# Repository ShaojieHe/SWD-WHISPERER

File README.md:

# SWD-WHISPERER
Custom DAPLink Hardware Design using AIR32F103Cx, This Version of hardware support SWD, JTAG, USB CDC, **ITM Trace/SWO**

Also this repo contain an [addon project](https://github.com/ShaojieHe/SWD-WHISPERER/tree/3225_crystal/standardJTAG_ADAPTER) to convert custom pinout to standard JTAG pinout for better debugging experience.

Licenced under CERN OHL v2 Permissive

## Pre-Built Custom DAPLink Firmware

[Github Repo](https://github.com/ShaojieHe/DAPLink-Extra)

[AIR32F10x Pre-Release](https://github.com/ShaojieHe/DAPLink-Extra/releases/tag/air32-pre-release)

## PCB Schematic
[Schematic](https://github.com/ShaojieHe/SWD-WHISPERER/blob/3225_crystal/DAPLink/air.pdf)

## PCB 3D Image

## How to Modify

This is an KiCad Project Design on version 6.0.9, You need an KiCad's Version > 6 to open it and play it around :)

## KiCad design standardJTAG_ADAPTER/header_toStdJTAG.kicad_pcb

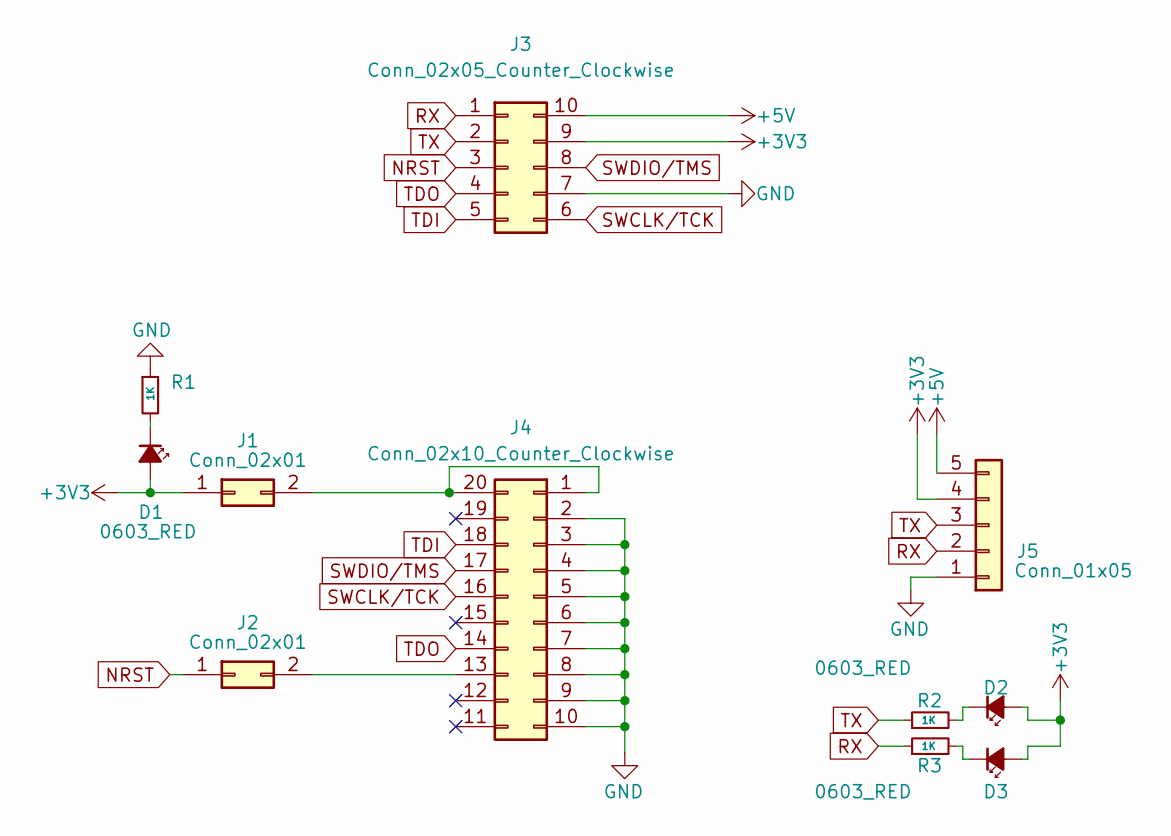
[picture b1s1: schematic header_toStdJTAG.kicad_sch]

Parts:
D1, D2, D3: 0603_RED; LED_0603_1608Metric
J1, J2: Conn_02x01; PinHeader_2x01_P2.54mm_Vertical
J3: Conn_02x05_Counter_Clockwise; 2.54_2X5
J4: Conn_02x10_Counter_Clockwise; 2.54_2X10
J5: Conn_01x05; PinHeader_1x05_P2.54mm_Vertical
R1, R2, R3: 1K; R_0603_1608Metric

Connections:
+3V3: D1.2 (A), D2.2 (A), D3.2 (A), J1.1, J3.9, J5.4
+5V: J3.10, J5.5
GND: J3.7, J4.2, J4.3, J4.4, J4.5, J4.6, J4.7, J4.8, J4.9, J4.10, J5.1, R1.1
NRST: J2.1, J3.3
unnamed: D1.1 (K), R1.2
unnamed: D2.1 (K), R2.2
unnamed: D3.1 (K), R3.2
unnamed: J1.2, J4.1, J4.20
unnamed: J2.2, J4.13
RX: J3.1, J5.2, R3.1
SWCLK/TCK: J3.6, J4.16
SWDIO/TMS: J3.8, J4.17
TDI: J3.5, J4.18
TDO: J3.4, J4.14
TX: J3.2, J5.3, R2.1

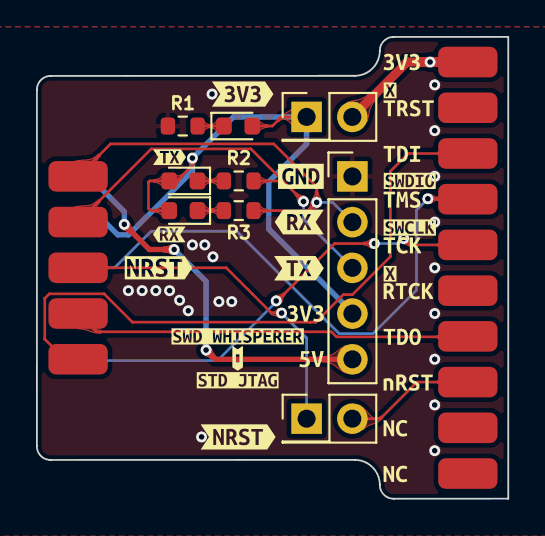
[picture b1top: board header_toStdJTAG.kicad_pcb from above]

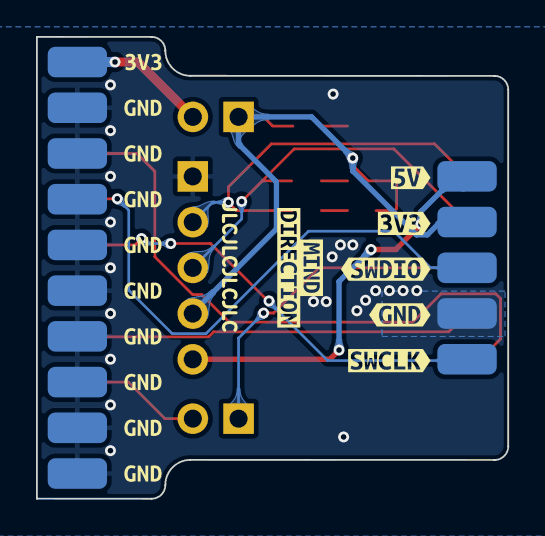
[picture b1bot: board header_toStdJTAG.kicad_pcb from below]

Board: 2 copper layers, 26.2 x 25.7 mm, 56 parts (18 on the bottom side), 15 nets.

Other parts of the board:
e: MY_LOGO
kibuzzard-632C5A4E: G***; kibuzzard-632C5A4E
kibuzzard-632C5A5B: G***; kibuzzard-632C5A5B
kibuzzard-632C5A6C: G***; kibuzzard-632C5A6C
kibuzzard-632C5A7C: G***; kibuzzard-632C5A7C
kibuzzard-632C5A8E: G***; kibuzzard-632C5A8E
kibuzzard-632C5A78: G***; kibuzzard-632C5A78
kibuzzard-632C5AAA: G***; kibuzzard-632C5AAA
kibuzzard-632C5AB4: G***; kibuzzard-632C5AB4
kibuzzard-632C5ABC: G***; kibuzzard-632C5ABC
kibuzzard-632C5B86: G***; kibuzzard-632C5B86
kibuzzard-632C5BCD: G***; kibuzzard-632C5BCD
kibuzzard-632C5CBE: G***; kibuzzard-632C5CBE
kibuzzard-632C5D1, kibuzzard-632C5D2, kibuzzard-632C5D3, kibuzzard-632C5D4, kibuzzard-632C5D5, kibuzzard-632C5D6, kibuzzard-632C5D7, kibuzzard-632C5D8, kibuzzard-632C5D89: G***; kibuzzard-632C5D89
kibuzzard-632C5D32: G***; kibuzzard-632C5D32
kibuzzard-632C5EE0: G***; kibuzzard-632C5EE0
kibuzzard-632C5EFB: G***; kibuzzard-632C5EFB
kibuzzard-632C5F3E: G***; kibuzzard-632C5F3E
kibuzzard-632C57D4: G***; kibuzzard-632C57D4
kibuzzard-632C57F8: G***; kibuzzard-632C57F8
kibuzzard-632C60B1: G***; kibuzzard-632C60B1
kibuzzard-632C60B5: G***; kibuzzard-632C60B5
kibuzzard-632C60E7: G***; kibuzzard-632C60E7
kibuzzard-632C575C: G***; kibuzzard-632C575C
kibuzzard-632C580A: G***; kibuzzard-632C580A
kibuzzard-632C584F: G***; kibuzzard-632C584F
kibuzzard-632C5768: G***; kibuzzard-632C5768
kibuzzard-632C5841: G***; kibuzzard-632C5841
kibuzzard-632C5933, kibuzzard-632C5933#2: G***; kibuzzard-632C5933
kibuzzard-632C6056: G***; kibuzzard-632C6056
kibuzzard-632C6067: G***; kibuzzard-632C6067
kibuzzard-632C6200, kibuzzard-632C6200#2: G***; kibuzzard-632C6200
kibuzzard-6336E20B: G***; kibuzzard-6336E20B
kibuzzard-6336E28C: G***; kibuzzard-6336E28C
kibuzzard-6336E204: G***; kibuzzard-6336E204

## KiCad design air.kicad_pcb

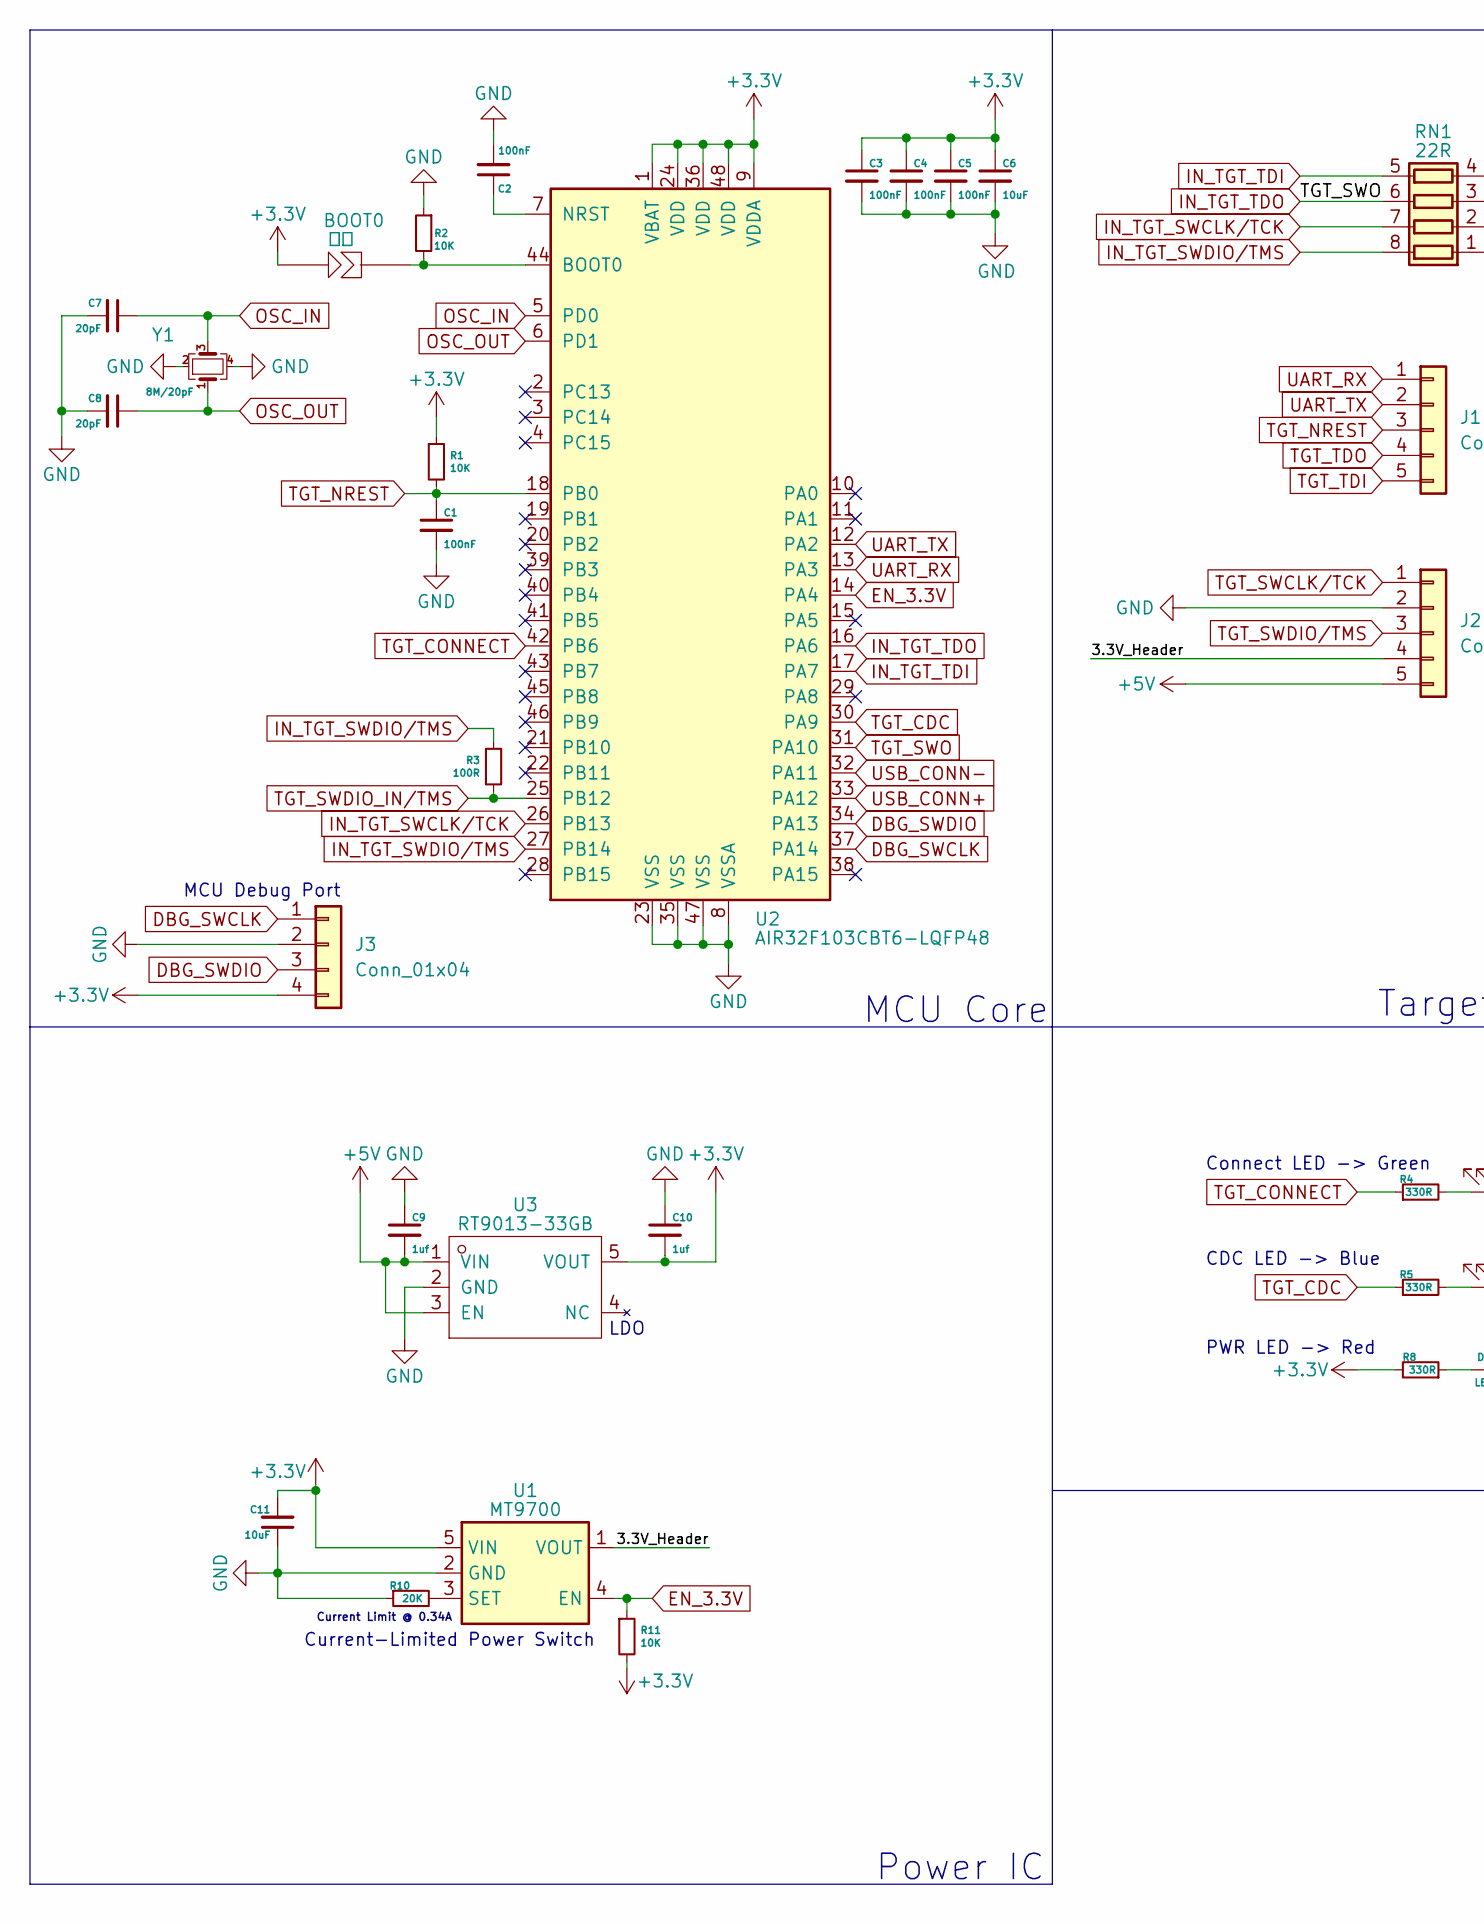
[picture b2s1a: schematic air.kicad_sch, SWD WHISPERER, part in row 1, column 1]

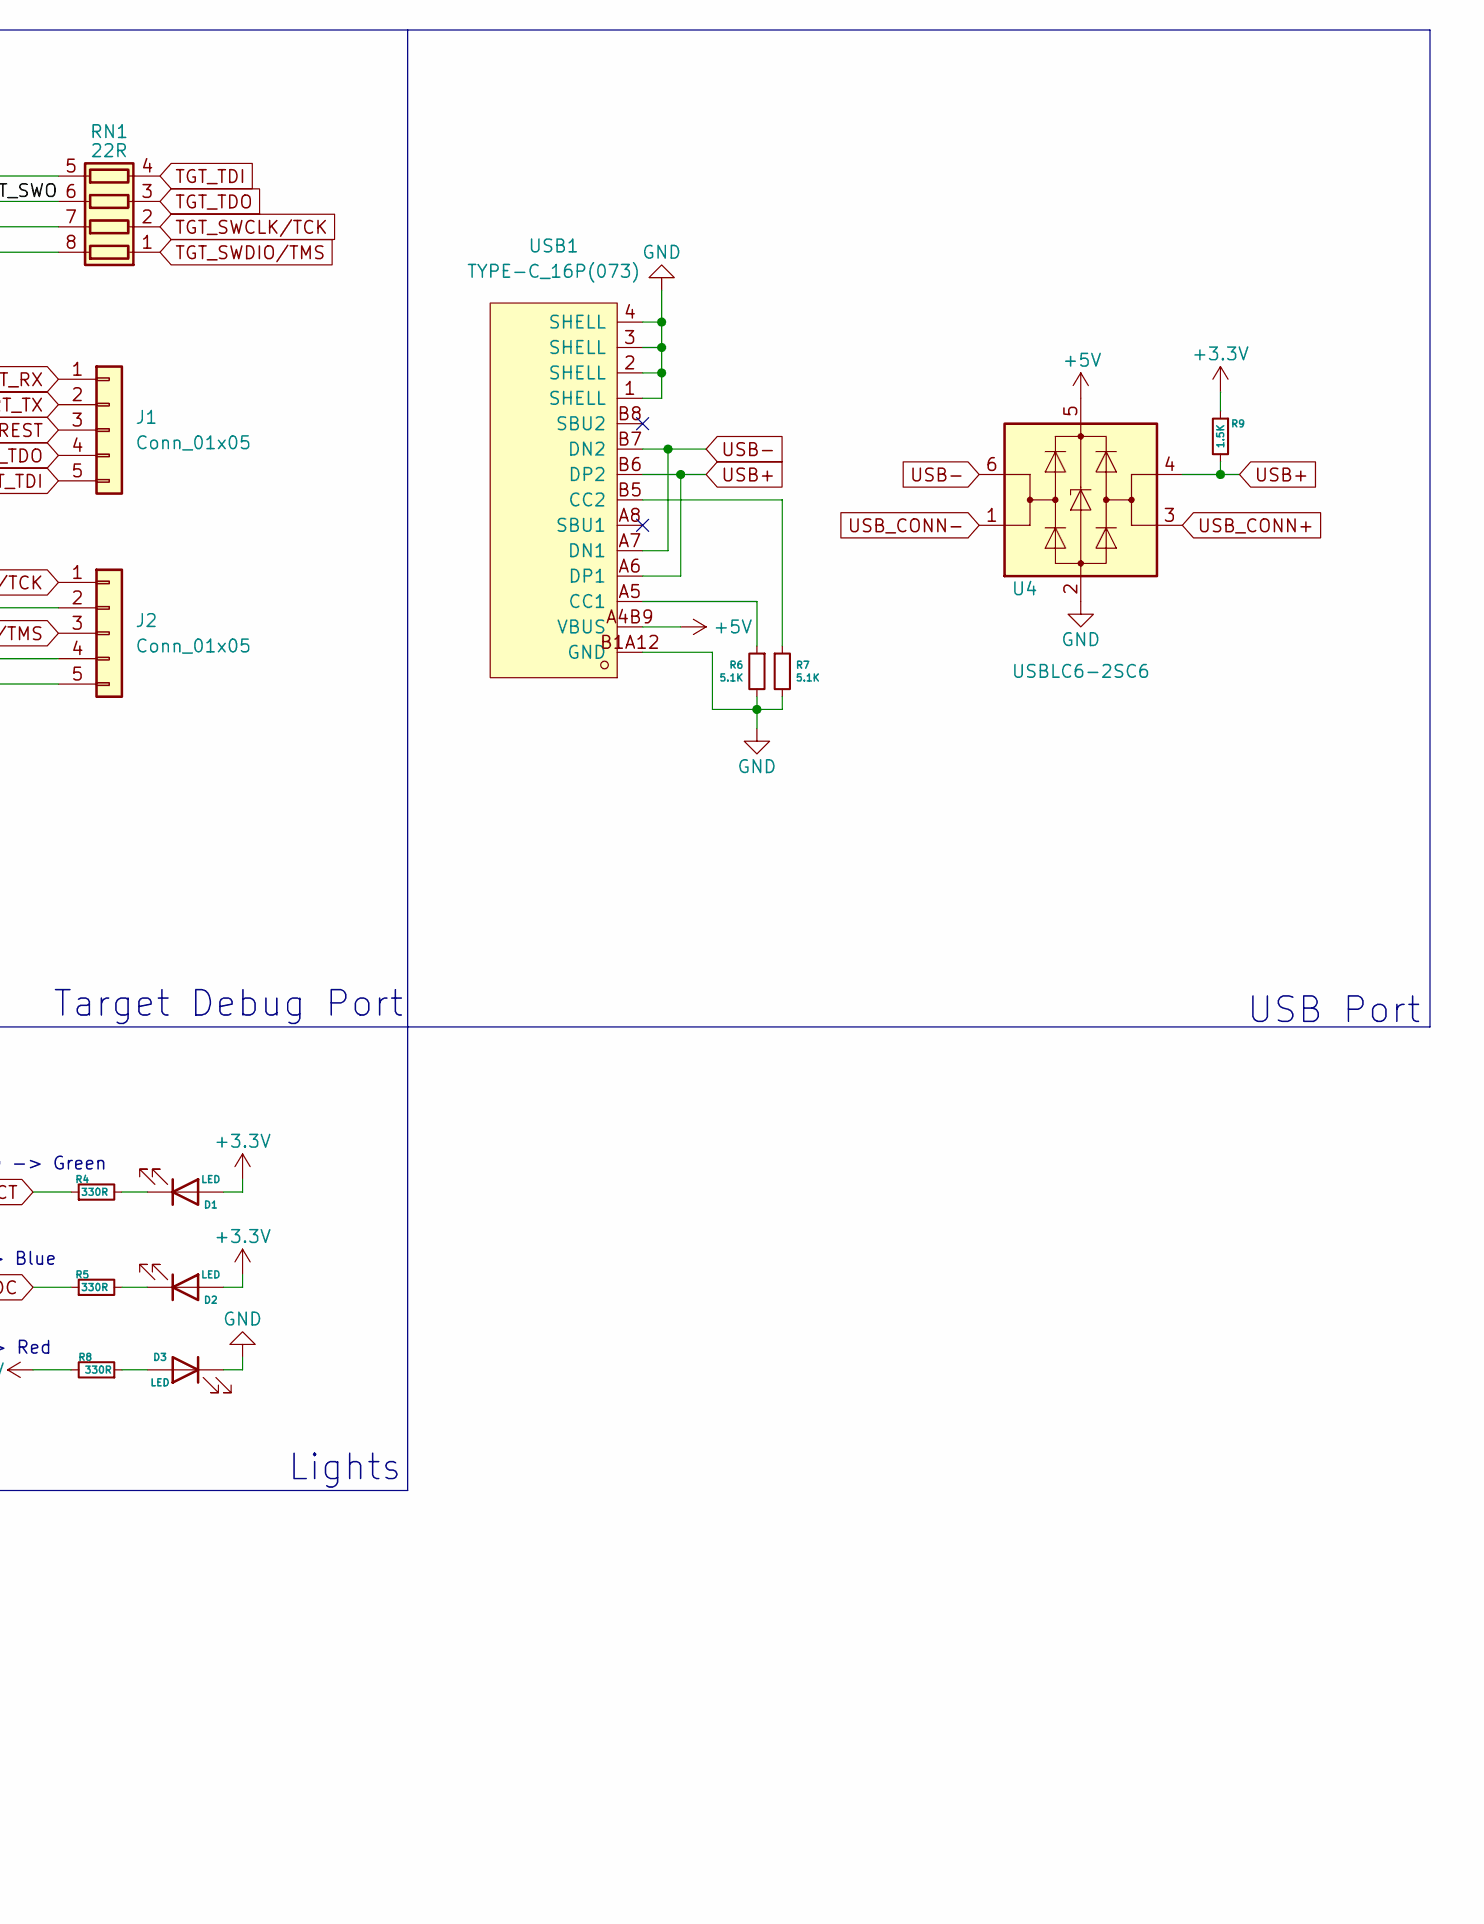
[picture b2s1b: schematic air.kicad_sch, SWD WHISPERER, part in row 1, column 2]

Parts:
BOOT0: 短接; Short_0603
C1, C2, C3, C4, C5: 100nF; C_0603_1608Metric
C6, C11: 10uF; C_0603_1608Metric
C7, C8: 20pF; C_0603_1608Metric
C9, C10: 1uf; C_0603_1608Metric
D1, D2, D3: LED; LED_0603_1608Metric
J1, J2: Conn_01x05; 2.54_1X5
J3: Conn_01x04; PinHeader_1x04_P1.27mm_Vertical
R1, R2, R11: 10K; R_0603_1608Metric
R3: 100R; R_0603_1608Metric
R4, R5, R8: 330R; R_0603_1608Metric
R6, R7: 5.1K; R_0603_1608Metric
R9: 1.5K; R_0603_1608Metric
R10: 20K; R_0603_1608Metric
RN1: 22R; R_Array_Convex_4x0603
U1: MT9700; SOT-23-5
U2: AIR32F103CBT6-LQFP48; LQFP-48_7x7mm_P0.5mm
U3: RT9013-33GB; SOT-23-5
U4: USBLC6-2SC6; SOT-23-6
USB1: TYPE-C_16P(073); USB-C-SMD_TYPE-C16PIN_C668624
Y1: 8M/20pF; Crystal_SMD_3225-4Pin_3.2x2.5mm

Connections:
+3.3V: BOOT0.1, C3.1, C4.1, C5.1, C6.1, C10.2, C11.2, D1.2 (A), D2.2 (A), J3.4, R1.1, R8.2, R9.1, R11.2, U1.5 (VIN), U2.1 (VBAT), U2.9 (VDDA), U2.24 (VDD), U2.36 (VDD), U2.48 (VDD), U3.5 (VOUT)
+5V: C9.2, J2.5, U3.1 (VIN), U3.3 (EN), U4.5 (VBUS), USB1.A4B9 (VBUS)
/3.3V_Header: J2.4, U1.1 (VOUT)
DBG_SWCLK: J3.1, U2.37 (PA14)
DBG_SWDIO: J3.3, U2.34 (PA13)
EN_3.3V: R11.1, U1.4 (EN), U2.14 (PA4)
GND: C1.2, C2.2, C3.2, C4.2, C5.2, C6.2, C7.2, C8.2, C9.1, C10.1, C11.1, D3.1 (K), J2.2, J3.2, R2.1, R6.2, R7.2, R10.1, U1.2 (GND), U2.8 (VSSA), U2.23 (VSS), U2.35 (VSS), U2.47 (VSS), U3.2 (GND), U4.2 (GND), USB1.1 (SHELL), USB1.2 (SHELL), USB1.3 (SHELL), USB1.4 (SHELL), USB1.A1B12 (GND), USB1.B1A12 (GND), Y1.2, Y1.4
IN_TGT_SWCLK/TCK: RN1.7 (R2.2), U2.26 (PB13)
IN_TGT_SWDIO/TMS: R3.1, RN1.8 (R1.2), U2.27 (PB14)
IN_TGT_TDI: RN1.5 (R4.2), U2.17 (PA7)
IN_TGT_TDO: RN1.6 (R3.2), U2.16 (PA6), U2.31 (PA10)
unnamed: BOOT0.2, R2.2, U2.44 (BOOT0)
unnamed: C2.1, U2.7 (NRST)
unnamed: D1.1 (K), R4.2
unnamed: D2.1 (K), R5.2
unnamed: D3.2 (A), R8.1
unnamed: R6.1, USB1.A5 (CC1)
unnamed: R7.1, USB1.B5 (CC2)
unnamed: R10.2, U1.3 (SET)
OSC_IN: C7.1, U2.5 (PD0), Y1.3
OSC_OUT: C8.1, U2.6 (PD1), Y1.1
TGT_CDC: R5.1, U2.30 (PA9)
TGT_CONNECT: R4.1, U2.42 (PB6)
TGT_NREST: C1.1, J1.3, R1.2, U2.18 (PB0)
TGT_SWCLK/TCK: J2.1, RN1.2 (R2.1)
TGT_SWDIO_IN/TMS: R3.2, U2.25 (PB12)
TGT_SWDIO/TMS: J2.3, RN1.1 (R1.1)
TGT_TDI: J1.5, RN1.4 (R4.1)
TGT_TDO: J1.4, RN1.3 (R3.1)
UART_RX: J1.1, U2.13 (PA3)
UART_TX: J1.2, U2.12 (PA2)
USB+: R9.2, U4.4 (I/O2), USB1.A6 (DP1), USB1.B6 (DP2)
USB-: U4.6 (I/O1), USB1.A7 (DN1), USB1.B7 (DN2)
USB_CONN+: U2.33 (PA12), U4.3 (I/O2)
USB_CONN-: U2.32 (PA11), U4.1 (I/O1)

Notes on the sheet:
CDC LED -> Blue
Target Debug Port
Lights
LDO
USB Port
MCU Core
Power IC
Current Limit @ 0.34A
Current-Limited Power Switch
PWR LED -> Red
Connect LED -> Green
MCU Debug Port

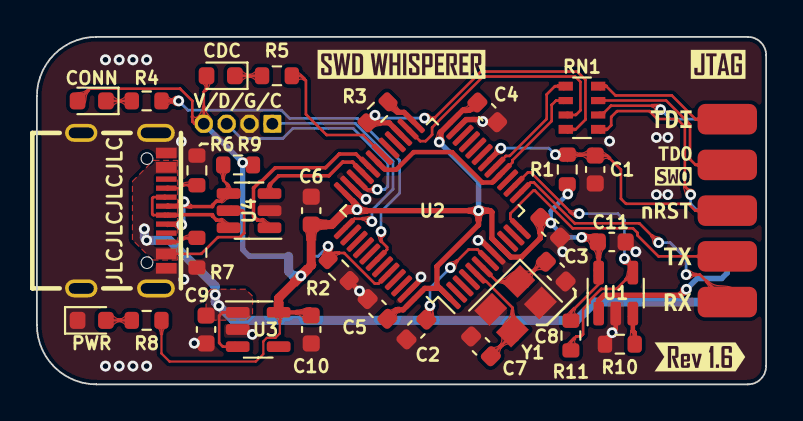
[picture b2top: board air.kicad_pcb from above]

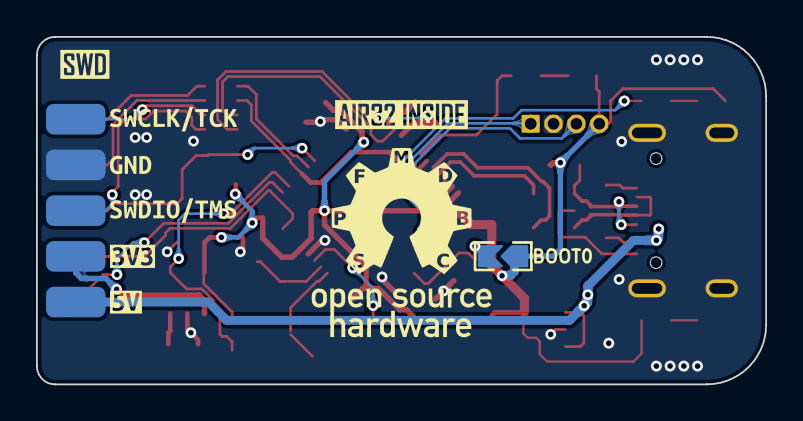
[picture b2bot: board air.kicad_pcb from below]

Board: 2 copper layers, 40.5 x 19.3 mm, 52 parts (9 on the bottom side), 35 nets.

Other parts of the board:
kibuzzard-62F961D8: G***; kibuzzard-62F961D8
kibuzzard-62F9645D: G***; kibuzzard-62F9645D
kibuzzard-62F96023: G***; kibuzzard-62F96023
kibuzzard-63A8965B: G***; kibuzzard-63A8965B
kibuzzard-637AECE1: G***; kibuzzard-637AECE1
kibuzzard-637AED1A: G***; kibuzzard-637AED1A
kibuzzard-6354CCE5: G***; kibuzzard-6354CCE5
kibuzzard-6354CCEF: G***; kibuzzard-6354CCEF
kibuzzard-6354CCF5: G***; kibuzzard-6354CCF5
kibuzzard-6354CD6B: G***; kibuzzard-6354CD6B
kibuzzard-6354CD34: G***; kibuzzard-6354CD34
kibuzzard-6354CD45: G***; kibuzzard-6354CD45
kibuzzard-6354CD83: G***; kibuzzard-6354CD83
kibuzzard-6354CD88: G***; kibuzzard-6354CD88
kibuzzard-6354CDA6: G***; kibuzzard-6354CDA6
kibuzzard-6354D1FB: G***; kibuzzard-6354D1FB

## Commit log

2022-10-23 V1.3版本更新
    第一版本更新 之前的都没包含在里面
2022-10-23 V1.3 3225晶振版本
2022-11-21 更新了SWO的硬件功能 从该板开始 可能不兼容上一代的固件
2022-11-26 v1.5 added series resistor on debug lines
2022-12-25 1.6 Redesign And Add Anti Reverse Current
2023-02-06 still 1.6 but contain some fix to publish work
2023-02-06 创建了 README.md
2023-02-06 添加了 CERN OHL v2 Permissive 开源协议
2023-02-06 add schematic of v1.6
2023-02-06 moved gerber file from repo to release
2023-02-06 更新了 README
2023-02-06 reloacted file to include new addon project
2023-02-06 add an addon project to include standardJTAG_Adapter
2023-02-06 更新了README
2023-02-06 replace Font with specimen/Teko
